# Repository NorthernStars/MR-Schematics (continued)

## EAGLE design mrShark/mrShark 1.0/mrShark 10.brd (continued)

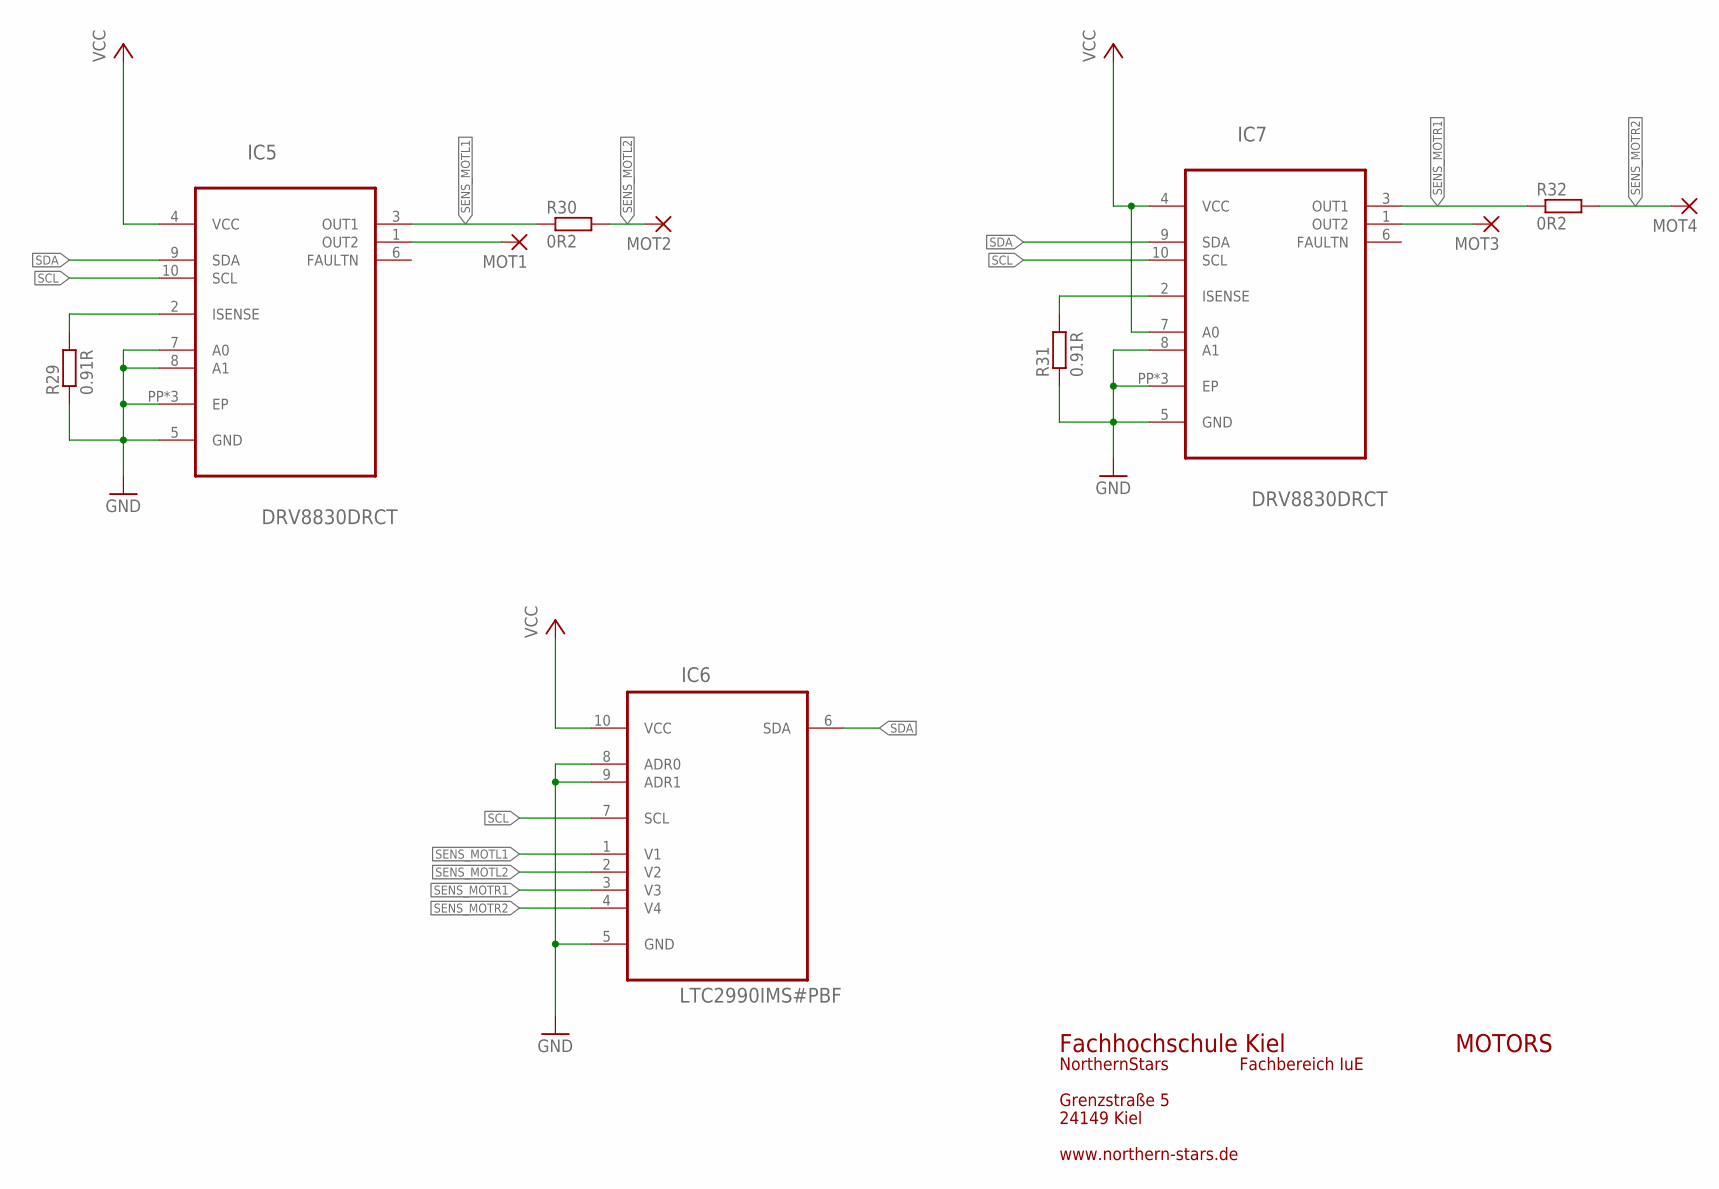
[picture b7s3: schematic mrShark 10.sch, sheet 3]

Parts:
IC5, IC7: DRV8830DRCT; S-PDSO-N10
IC6: LTC2990IMS#PBF; SOP50P490X110-10N
MOT1, MOT2, MOT3, MOT4: 1,6/0,9
R29, R31: 0.91R; R0603
R30, R32: 0R2; R0603

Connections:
GND: IC5.5 (GND), IC5.7 (A0), IC5.8 (A1), IC5.PP (EP), IC5.PP@1 (EP), IC5.PP@2 (EP), IC6.5 (GND), IC6.8 (ADR0), IC6.9 (ADR1), IC7.5 (GND), IC7.8 (A1), IC7.PP (EP), IC7.PP@1 (EP), IC7.PP@2 (EP), R29.1, R31.1; also elsewhere on the board
unnamed: IC5.1 (OUT2), MOT1.1
unnamed: IC5.2 (ISENSE), R29.2
unnamed: IC7.1 (OUT2), MOT3.1
unnamed: IC7.2 (ISENSE), R31.2
SCL: IC5.10 (SCL), IC6.7 (SCL), IC7.10 (SCL); also elsewhere on the board
SDA: IC5.9 (SDA), IC6.6 (SDA), IC7.9 (SDA); also elsewhere on the board
SENS_MOTL1: IC5.3 (OUT1), IC6.1 (V1), R30.1
SENS_MOTL2: IC6.2 (V2), MOT2.1, R30.2
SENS_MOTR1: IC6.3 (V3), IC7.3 (OUT1), R32.1
SENS_MOTR2: IC6.4 (V4), MOT4.1, R32.2
VCC: IC5.4 (VCC), IC6.10 (VCC), IC7.4 (VCC), IC7.7 (A0); also elsewhere on the board

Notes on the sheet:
MOTORS
Fachhochschule Kiel
Grenzstraße 5
24149 Kiel
NorthernStars
Fachbereich IuE
www.northern-stars.de

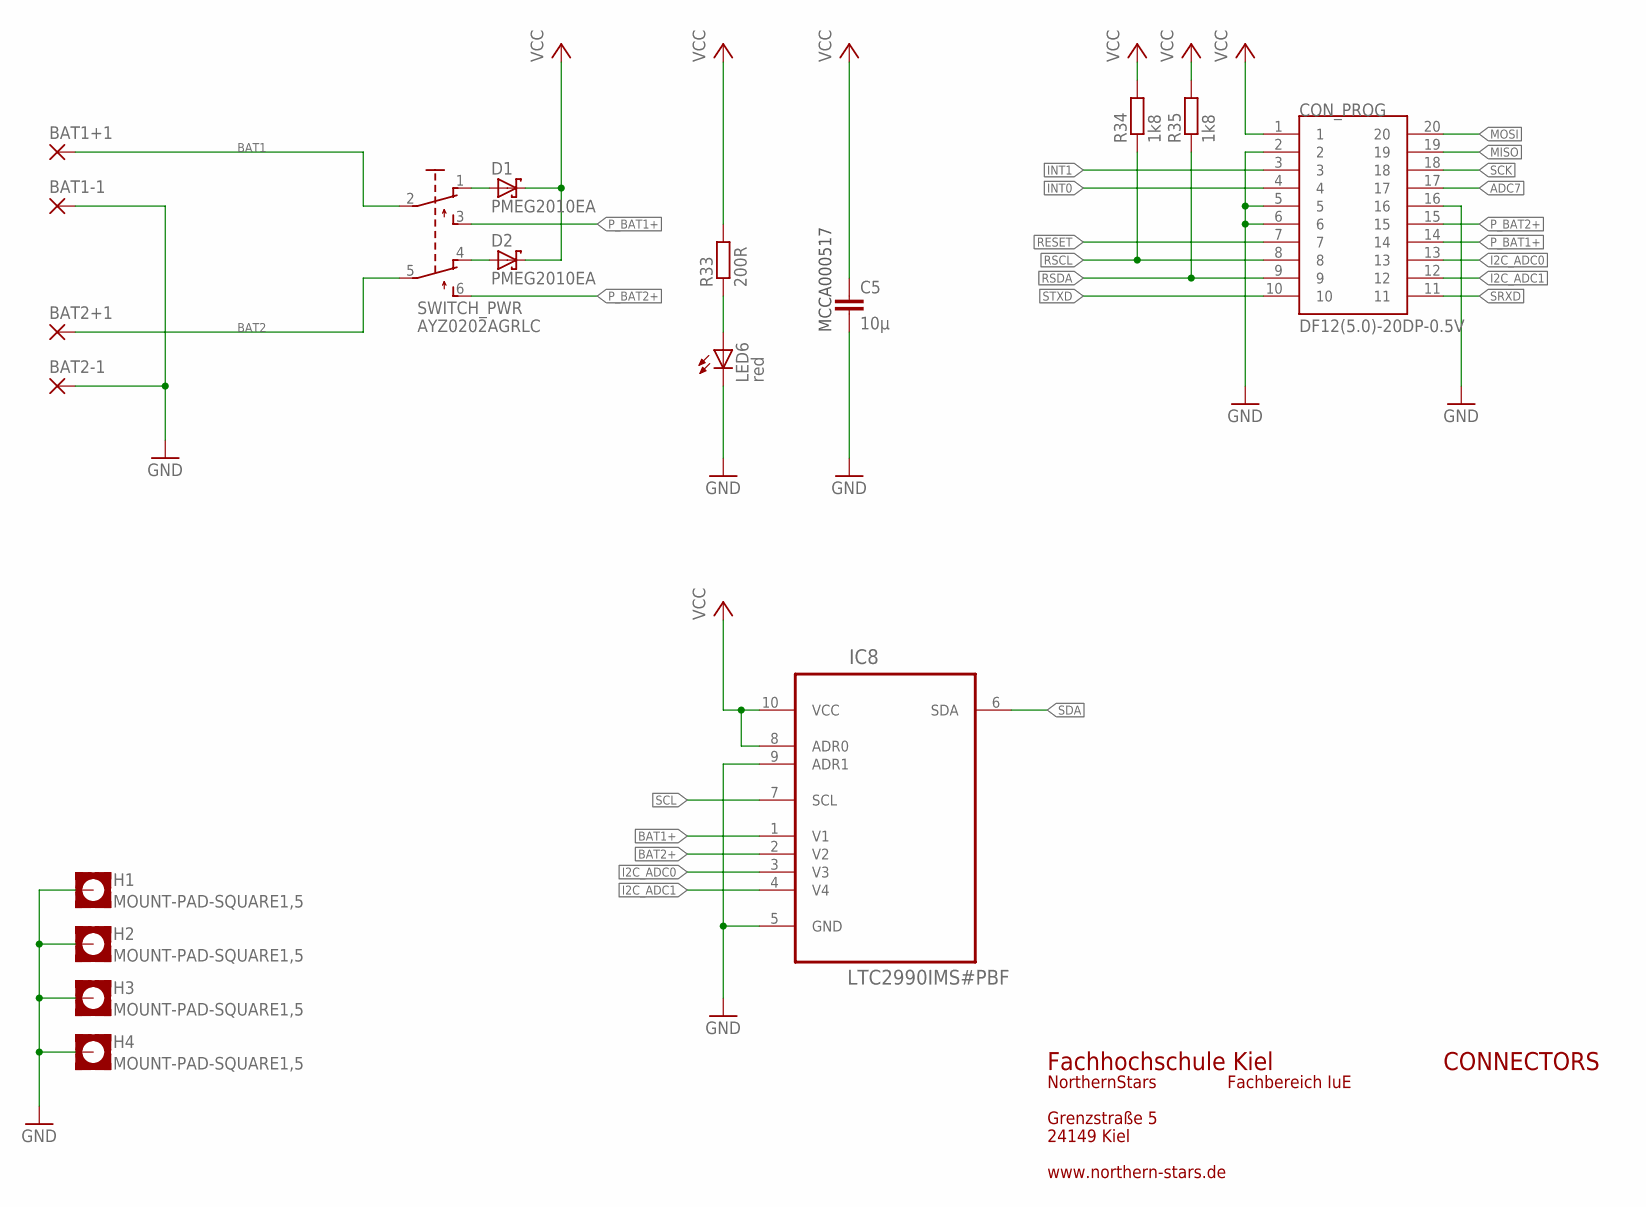
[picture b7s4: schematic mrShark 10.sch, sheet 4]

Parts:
BAT1+1, BAT1-1, BAT2+1, BAT2-1: 1,6/0,9
C5: 10µ; C0603K
CON_PROG: DF12(5.0)-20DP-0.5V; DF12-20DP
D1, D2: PMEG2010EA; SOD323-R
H1, H2, H3, H4: MOUNT-PAD-SQUARE1,5; 0,75-PAD-SQUARE
IC8: LTC2990IMS#PBF; SOP50P490X110-10N
LED6: red; CHIPLED_0603
R33: 200R; R0201
R34, R35: 1k8; R0201
SWITCH_PWR: AYZ0202AGRLC; AYZ0202AGLRC

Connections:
ADC7: CON_PROG.17; also elsewhere on the board
BAT1: BAT1+1.1, SWITCH_PWR.2
BAT1+: D1.A, IC8.1 (V1), SWITCH_PWR.1 (O)
BAT2: BAT2+1.1, SWITCH_PWR.5 (P1)
BAT2+: D2.A, IC8.2 (V2), SWITCH_PWR.4 (O1)
GND: BAT1-1.1, BAT2-1.1, C5.2, CON_PROG.2, CON_PROG.5, CON_PROG.6, CON_PROG.16, H1.P, H2.P, H3.P, H4.P, IC8.5 (GND), IC8.9 (ADR1), LED6.C; also elsewhere on the board
I2C_ADC0: CON_PROG.13, IC8.3 (V3)
I2C_ADC1: CON_PROG.12, IC8.4 (V4)
INT0: CON_PROG.4; also elsewhere on the board
INT1: CON_PROG.3; also elsewhere on the board
MISO: CON_PROG.19; also elsewhere on the board
MOSI: CON_PROG.20; also elsewhere on the board
unnamed: LED6.A, R33.1
P_BAT1+: CON_PROG.14, SWITCH_PWR.3 (S)
P_BAT2+: CON_PROG.15, SWITCH_PWR.6 (S1)
RESET: CON_PROG.7; also elsewhere on the board
RSCL: CON_PROG.8, R34.1; also elsewhere on the board
RSDA: CON_PROG.9, R35.1; also elsewhere on the board
SCK: CON_PROG.18; also elsewhere on the board
SCL: IC8.7 (SCL); also elsewhere on the board
SDA: IC8.6 (SDA); also elsewhere on the board
SRXD: CON_PROG.11; also elsewhere on the board
STXD: CON_PROG.10; also elsewhere on the board
VCC: C5.1, CON_PROG.1, D1.C, D2.C, IC8.8 (ADR0), IC8.10 (VCC), R33.2, R34.2, R35.2; also elsewhere on the board

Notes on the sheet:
CONNECTORS
Fachhochschule Kiel
Grenzstraße 5
24149 Kiel
NorthernStars
Fachbereich IuE
www.northern-stars.de
MCCA000517

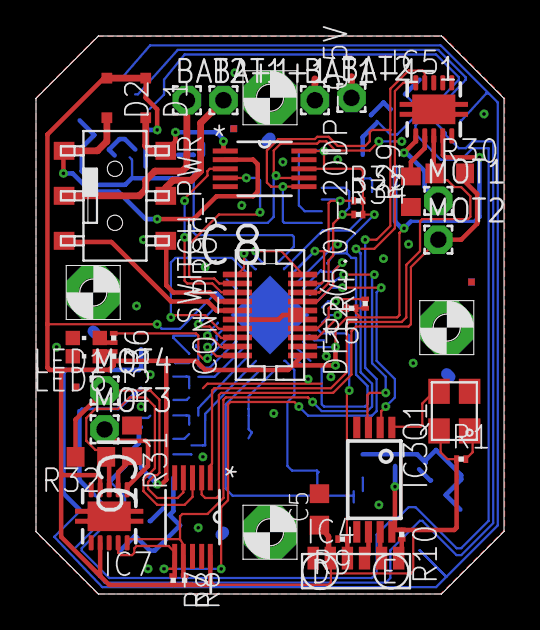
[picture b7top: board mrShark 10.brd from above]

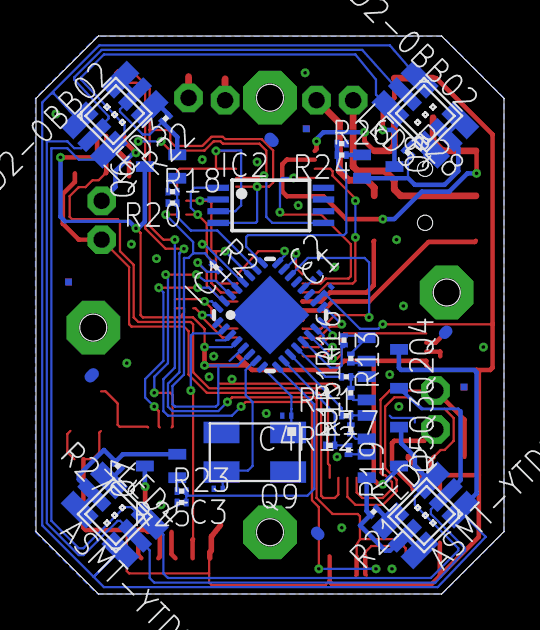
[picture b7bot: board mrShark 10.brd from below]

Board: 2 copper layers, 26.0 x 31.0 mm, 78 parts (37 on the bottom side), 70 nets.
